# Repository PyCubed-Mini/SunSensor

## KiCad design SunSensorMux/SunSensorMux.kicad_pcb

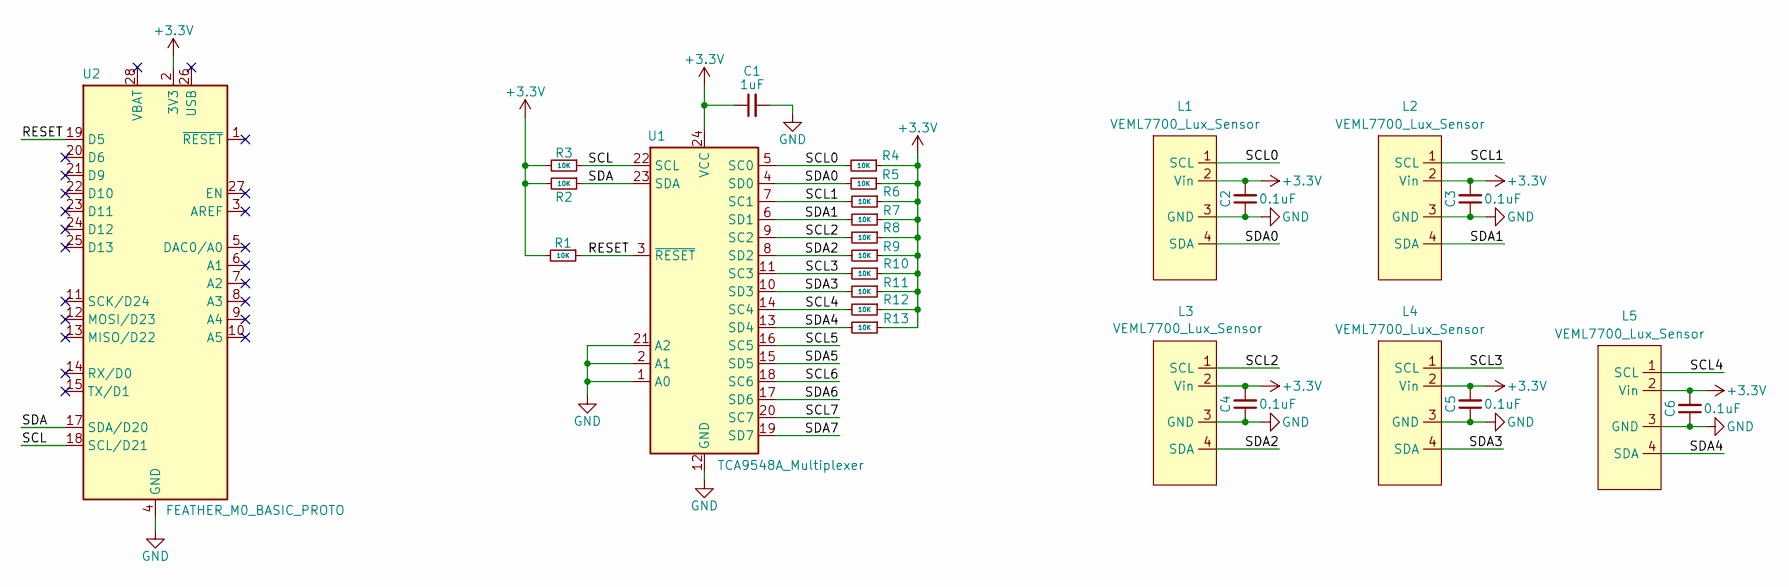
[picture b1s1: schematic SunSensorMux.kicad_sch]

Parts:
C1: 1uF; C_0603_1608Metric
C2, C3, C4, C5, C6: 0.1uF; C_0603_1608Metric
L1, L2, L3, L4, L5: VEML7700_Lux_Sensor; VEML7700-TT
R1, R2, R3, R4, R5, R6, R7, R8, R9, R10, R11, R12, R13: 10K; R_0603_1608Metric
U1: TCA9548A_Multiplexer; TSSOP-24_4.4x7.8mm_P0.65mm
U2: FEATHER_M0_BASIC_PROTO; Adafruit_Feather

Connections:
+3.3V: C1.1, C2.2, C3.2, C4.2, C5.2, C6.2, L1.2 (Vin), L2.2 (Vin), L3.2 (Vin), L4.2 (Vin), L5.2 (Vin), R1.2, R2.2, R3.2, R4.1, R5.1, R6.1, R7.1, R8.1, R9.1, R10.1, R11.1, R12.1, R13.1, U1.24 (VCC), U2.2 (3V3)
/RESET: R1.1, U1.3 (~RESET), U2.19 (D5)
/SCL: R3.1, U1.22 (SCL), U2.18 (SCL/D21)
/SCL0: L1.1 (SCL), R4.2, U1.5 (SC0)
/SCL1: L2.1 (SCL), R6.2, U1.7 (SC1)
/SCL2: L3.1 (SCL), R8.2, U1.9 (SC2)
/SCL3: L4.1 (SCL), R10.2, U1.11 (SC3)
/SCL4: L5.1 (SCL), R12.2, U1.14 (SC4)
/SCL5: U1.16 (SC5)
/SCL6: U1.18 (SC6)
/SCL7: U1.20 (SC7)
/SDA: R2.1, U1.23 (SDA), U2.17 (SDA/D20)
/SDA0: L1.4 (SDA), R5.2, U1.4 (SD0)
/SDA1: L2.4 (SDA), R7.2, U1.6 (SD1)
/SDA2: L3.4 (SDA), R9.2, U1.8 (SD2)
/SDA3: L4.4 (SDA), R11.2, U1.10 (SD3)
/SDA4: L5.4 (SDA), R13.2, U1.13 (SD4)
/SDA5: U1.15 (SD5)
/SDA6: U1.17 (SD6)
/SDA7: U1.19 (SD7)
GND: C1.2, C2.1, C3.1, C4.1, C5.1, C6.1, L1.3 (GND), L2.3 (GND), L3.3 (GND), L4.3 (GND), L5.3 (GND), U1.1 (A0), U1.2 (A1), U1.12 (GND), U1.21 (A2), U2.4 (GND), U2.16 (GND)

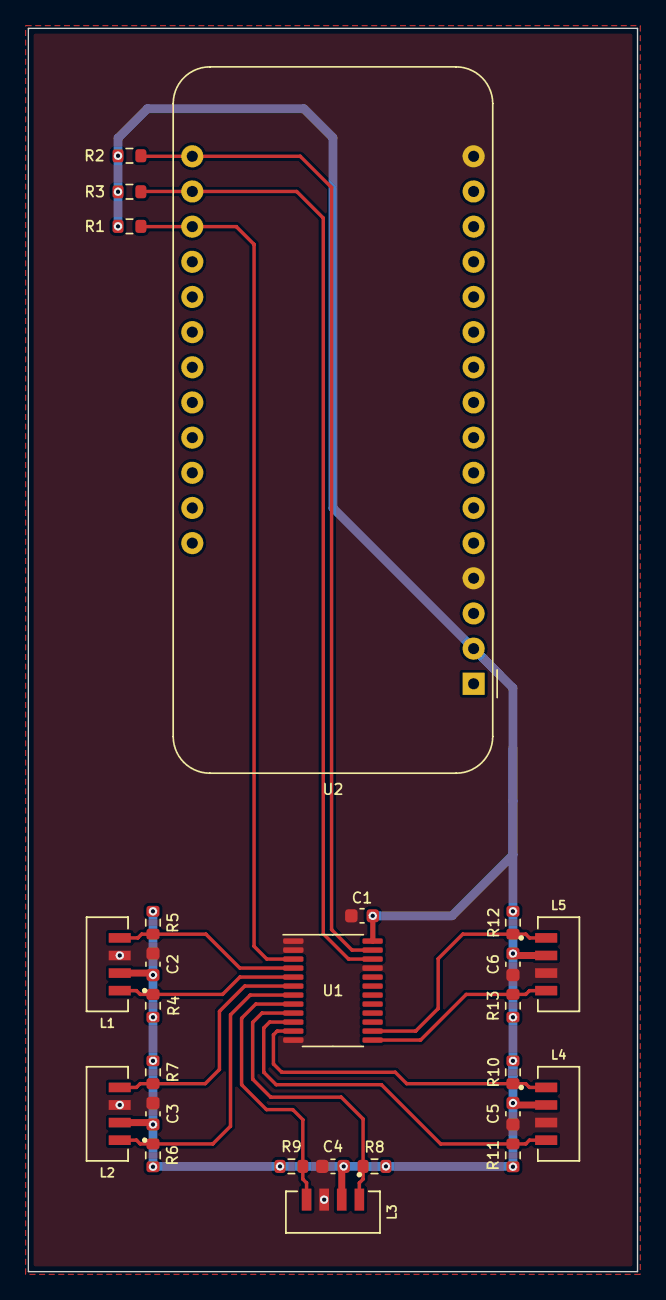
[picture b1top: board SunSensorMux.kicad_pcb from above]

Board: 2 copper layers, 44.0 x 89.8 mm, 26 parts (0 on the bottom side), 15 nets.

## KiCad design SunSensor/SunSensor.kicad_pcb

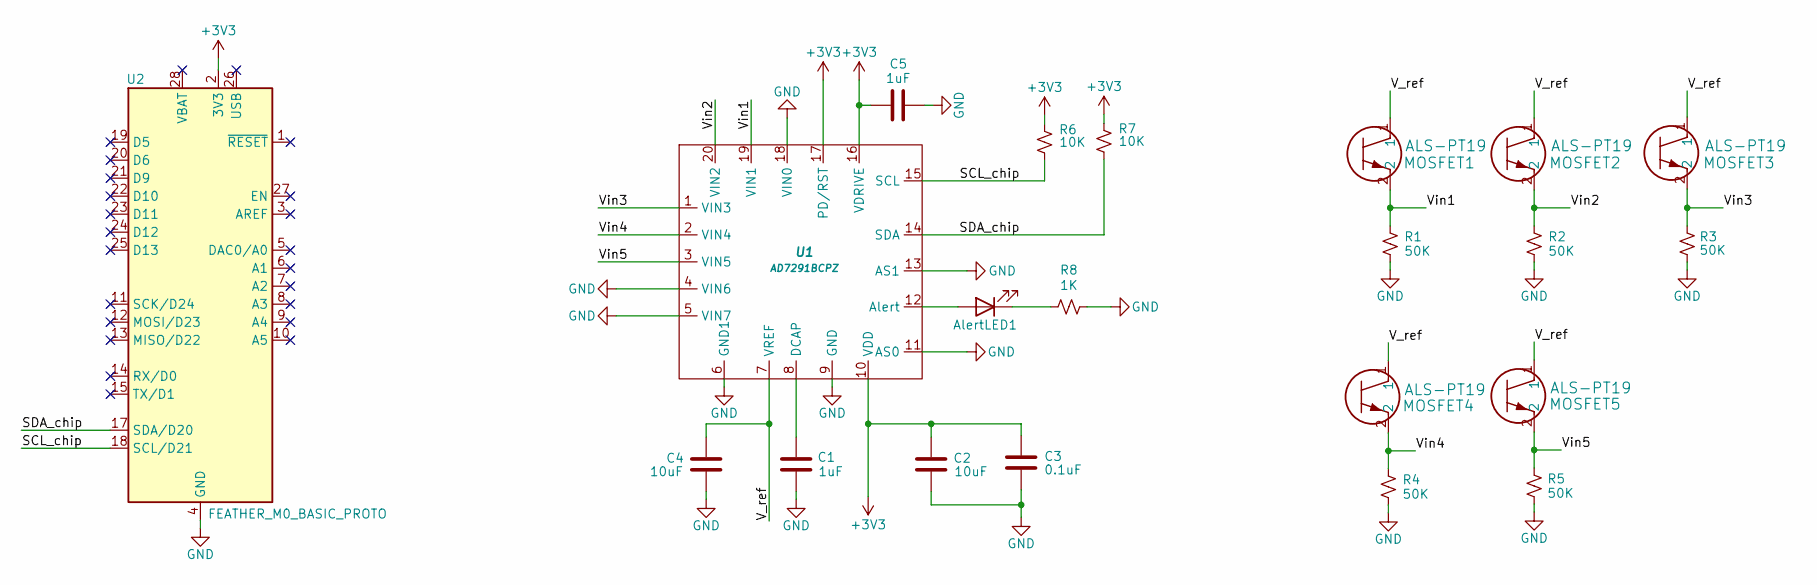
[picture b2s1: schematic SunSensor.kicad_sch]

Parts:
AlertLED1: LED_0603_1608Metric
C1, C5: 1uF; C_0603_1608Metric
C2, C4: 10uF; C_0603_1608Metric
C3: 0.1uF; C_0603_1608Metric
MOSFET1, MOSFET2, MOSFET3, MOSFET4, MOSFET5: ALS-PT19; LED_77&slash_TR8_EVE
R1, R2, R3, R4, R5: 50K; R_0603_1608Metric
R6, R7: 10K; R_0603_1608Metric
R8: 1K; R_0603_1608Metric
U1: AD7291BCPZ; QFN-20-1EP_4x4mm_P0.5mm_EP2.6x2.6mm
U2: FEATHER_M0_BASIC_PROTO; Adafruit_Feather

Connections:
+3V3: C2.1, C3.1, C5.2, R6.2, R7.2, U1.10 (VDD), U1.16 (VDRIVE), U1.17 (PD/RST), U2.2 (3V3)
/SCL_chip: R6.1, U1.15 (SCL), U2.18 (SCL/D21)
/SDA_chip: R7.1, U1.14 (SDA), U2.17 (SDA/D20)
/V_ref: C4.1, MOSFET1.1, MOSFET2.1, MOSFET3.1, MOSFET4.1, MOSFET5.1, U1.7 (VREF)
/Vin1: MOSFET1.2, R1.1, U1.19 (VIN1)
/Vin2: MOSFET2.2, R2.1, U1.20 (VIN2)
/Vin3: MOSFET3.2, R3.1, U1.1 (VIN3)
/Vin4: MOSFET4.2, R4.1, U1.2 (VIN4)
/Vin5: MOSFET5.2, R5.1, U1.3 (VIN5)
GND: C1.2, C2.2, C3.2, C4.2, C5.1, R1.2, R2.2, R3.2, R4.2, R5.2, R8.2, U1.4 (VIN6), U1.5 (VIN7), U1.6 (GND1), U1.9 (GND), U1.11 (AS0), U1.13 (AS1), U1.18 (VIN0), U1.21 (GND), U2.4 (GND), U2.16 (GND)
unnamed 10: AlertLED1.2 (A), U1.12 (Alert); also elsewhere on the board
unnamed 11: AlertLED1.1 (K), R8.1; also elsewhere on the board
unnamed: C1.1, U1.8 (DCAP)

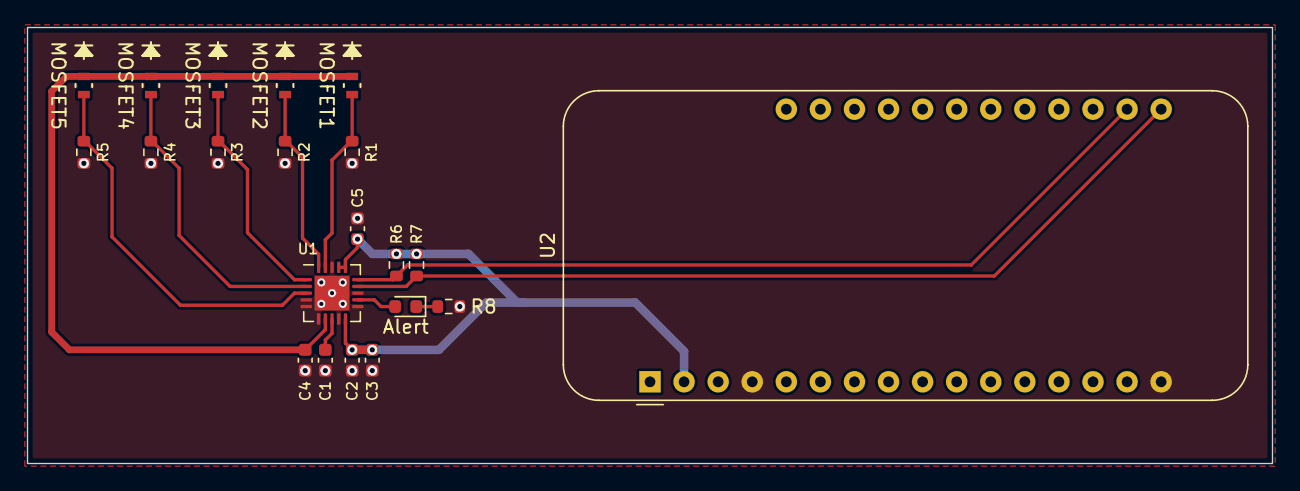
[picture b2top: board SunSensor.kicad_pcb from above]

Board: 2 copper layers, 92.8 x 32.5 mm, 21 parts (0 on the bottom side), 13 nets.

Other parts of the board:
Alert: LED_0603_1608Metric

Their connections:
unnamed 10: Alert.2 (A); also elsewhere on the board
unnamed 11: Alert.1 (K); also elsewhere on the board

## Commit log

2023-02-06 Finished schematic and finalized parts
2023-02-11 Added footprints and library to Sunsensor
2023-02-11 Added sunsensor.pretty to kicad-libs
2023-02-20 Fixed net issues
2023-02-27 fixing kicad-libs
2023-02-27 working on kicad-libs
2023-02-27 fixed kicad-libs
2023-03-06 finished board
2023-03-12 Finished traces
2023-04-10 Final modifications
2023-04-17 Small fixes
2023-04-17 more small changes
2023-04-24 final commit
2023-04-28 Finish Routing
2023-04-28 Update submodules
2023-04-28 misc
2023-05-26 Exported BOMs
2023-05-31 Code that makes the sun sensors work
    Just an infinite loop that reads the lux value from the sensors and shows that it responds to changes in light properly.
2023-06-07 Remove extraneous files
